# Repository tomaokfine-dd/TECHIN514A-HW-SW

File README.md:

# Screen Usage Load Meter

## 1. Project Overview

### What it does

Screen Usage Load Meter is a two-device system that estimates a user's screen usage load based on ambient light and user presence detection.  
A sensing device placed near a screen detects usage patterns, while a desktop display device visualizes the accumulated load using an analog gauge with a stepper motor and LED indicator.

### General Physical Sketch

The system consists of a small sensing module mounted near a computer screen and a desktop gauge display with a needle and LED.

---

## 2. Sensor Device

The sensor device is a compact, battery-powered module placed near a computer screen.  
It passively detects screen usage behavior without accessing the operating system and wirelessly transmits processed data to the display device via ESP-NOW.

### Sensors and Part Numbers

- **Ambient Light Sensor:** VEML7700 (Adafruit breakout)  
  Used to detect screen-on activity based on lux threshold (< 30 lux = screen off).
- **Time-of-Flight Distance Sensor:** VL53L4CX (Adafruit breakout)  
  Used to detect user presence in front of the screen (> 800mm = no person).

### Processor and Wireless

- **MCU + Wireless:** Seeed Studio XIAO ESP32C3 (ESP32-C3, ESP-NOW over Wi-Fi)

### Power

- 3.7V LiPo battery (1000 mAh)
- Onboard charging via XIAO ESP32C3 built-in battery management

### Sensor Device Sketch

The sensing module is mounted near the display, with the light sensor facing the screen and the distance sensor facing the user.  
The device operates autonomously and does not include user-facing controls.

---

## 3. Display Device

The display device is a desktop physical gauge that visualizes the current screen usage load.  
It integrates a stepper-motor-driven needle and an LED indicator, connected via breadboard prototype.

### Interface Components

- **Stepper Motor:** X27.168 bipolar gauge motor  
  Drives the gauge needle (2° per minute, full range 360°, returns to origin at 180 minutes).
- **LED:** NeoPixel WS2812B (single RGB LED for status indication)  
  Green (0–60 min) → Yellow (60–120 min) → Orange (120–180 min) → Bright Red (180+ min)

### Processor and Wireless

- **MCU + Wireless:** Seeed Studio XIAO ESP32C3  
  Receives data from the sensor device via ESP-NOW and controls motor and LED output.

### Power

- USB 5V (runs alongside computer)

### Display Device Sketch

The display features a gauge with a needle indicating cumulative usage load.  
An LED provides color-coded status, changing color every hour to indicate increasing usage intensity.

---

## 4. Communication and System Diagram

The sensor device continuously transmits processed usage data to the display device using **ESP-NOW** (peer-to-peer Wi-Fi protocol, no router required). The system converts raw sensor signals into a cumulative screen usage time that controls the gauge needle position and LED color state.

**Data Flow:**

1. Sensor signals (ambient light lux + distance mm)
2. Threshold logic (lux < 30 = screen off; distance > 800mm = no person)
3. Usage timer accumulation (seconds counted when both conditions met)
4. ESP-NOW transmission (minutes sent every second to display device)
5. Output mapping to needle position (2°/min) and LED color stage

---

## 5. DSP and Signal Processing Approach

- **DSP:**  
  Dual-threshold detection logic combines ambient light and distance signals. Screen-off state is detected when lux drops below 30. User absence is detected when ToF distance exceeds 800mm. Usage time accumulates only when both sensors confirm active use simultaneously.
- **Note:**  
  No ML model is used in the current implementation. Detection is rule-based with fixed thresholds calibrated to typical indoor desktop environments. False positive rate is approximately 5%, primarily caused by ambient light changes such as overhead lighting.

---

## 6. Datasheets

All component datasheets are included in the `/datasheets` folder, including:

- ESP32-C3 (Seeed Studio XIAO ESP32C3)
- VEML7700 Ambient Light Sensor (Vishay / Adafruit breakout)
- VL53L4CX Time-of-Flight Distance Sensor (ST / Adafruit breakout)
- X27.168 Bipolar Gauge Stepper Motor (Switec/Juken)
- WS2812B RGB LED (NeoPixel)
- Custom Sensor Board PCB (KiCad design files)

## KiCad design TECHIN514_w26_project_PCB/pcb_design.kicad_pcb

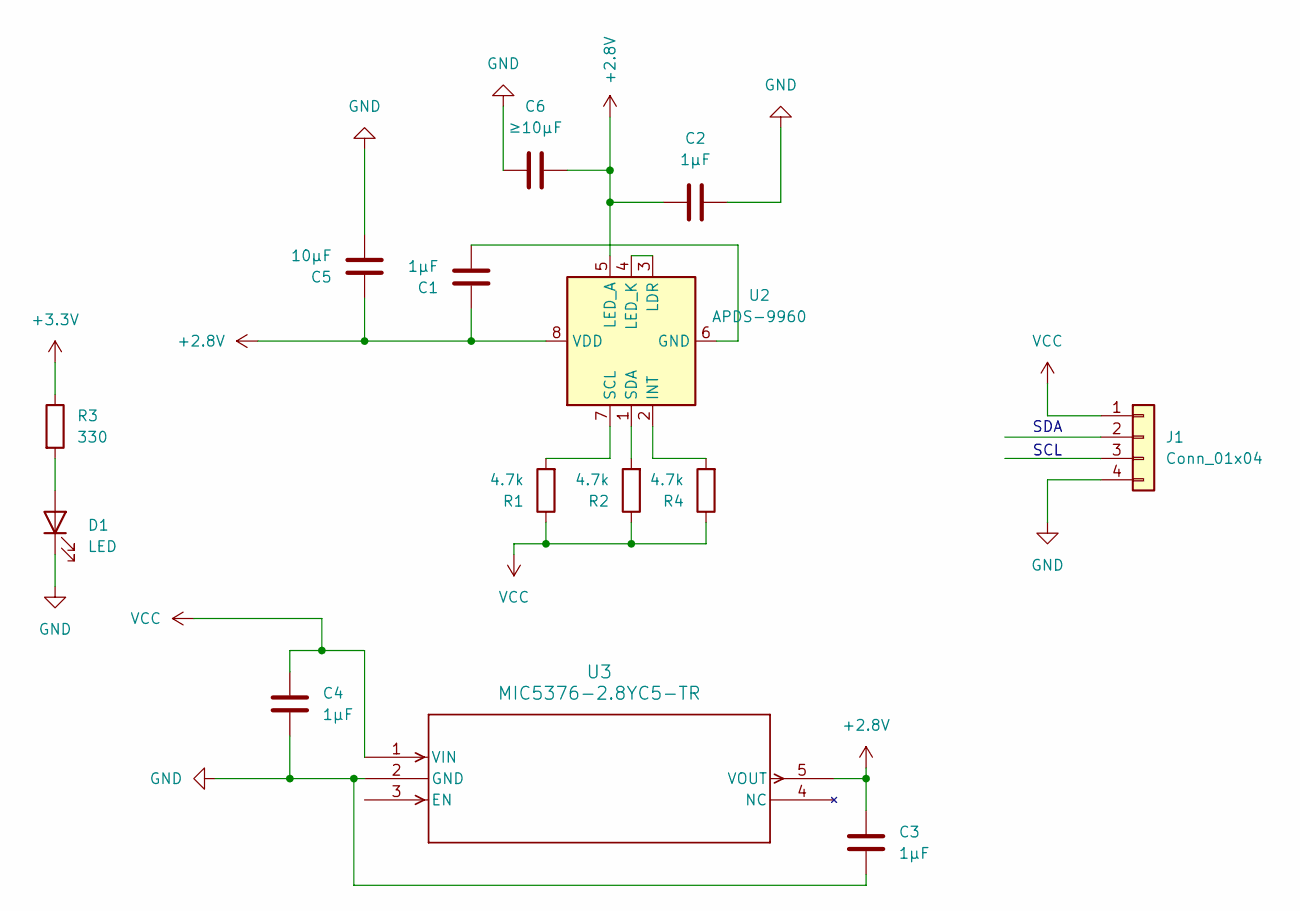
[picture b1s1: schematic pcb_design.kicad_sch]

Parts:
C1, C2, C3, C4: 1μF; C_0603_1608Metric_Pad1.08x0.95mm_HandSolder
C5: 10μF; C_0603_1608Metric_Pad1.08x0.95mm_HandSolder
C6: ≥10µF; C_0603_1608Metric_Pad1.08x0.95mm_HandSolder
D1: LED; LED_0603_1608Metric_Pad1.05x0.95mm_HandSolder
J1: Conn_01x04; PinSocket_1x04_P1.00mm_Vertical
R1, R2, R4: 4.7k; R_0603_1608Metric_Pad0.98x0.95mm_HandSolder
R3: 330; R_0603_1608Metric_Pad0.98x0.95mm_HandSolder
U2: APDS-9960; Avago_APDS-9960
U3: MIC5376-2.8YC5-TR; SC-70_C5_MCH

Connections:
+2.8V: C1.1, C2.1, C3.1, C5.1, C6.1, U2.5 (LED_A), U2.8 (VDD), U3.5 (VOUT)
+3.3V: R3.1
GND: C2.2, C3.2, C4.2, C5.2, C6.2, D1.1 (K), J1.4, U3.2 (GND)
unnamed: D1.2 (A), R3.2
unnamed: C1.2, U2.6 (GND)
unnamed: R4.2, U2.2 (INT)
unnamed: U2.3 (LDR), U2.4 (LED_K)
unnamed: R1.2, U2.7 (SCL)
unnamed: R2.2, U2.1 (SDA)
VCC: C4.1, J1.1, R1.1, R2.1, R4.1, U3.1 (VIN)

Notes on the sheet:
SDA
SCL

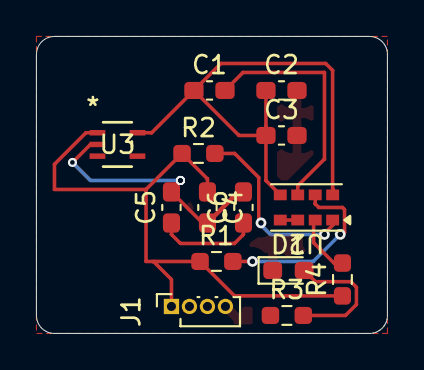
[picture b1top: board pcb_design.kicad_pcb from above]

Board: 2 copper layers, 19.5 x 16.5 mm, 14 parts (0 on the bottom side), 9 nets.

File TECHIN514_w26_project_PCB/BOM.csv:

"Reference","Qty","Value","DNP","Exclude from BOM","Exclude from Board","Footprint","Datasheet"
"C1,C2,C3,C4","4","1μF","","","","Capacitor_SMD:C_0603_1608Metric_Pad1.08x0.95mm_HandSolder","~"
"C5","1","10μF","","","","Capacitor_SMD:C_0603_1608Metric_Pad1.08x0.95mm_HandSolder","~"
"C6","1","≥10µF","","","","Capacitor_SMD:C_0603_1608Metric_Pad1.08x0.95mm_HandSolder","~"
"D1","1","LED","","","","LED_SMD:LED_0603_1608Metric_Pad1.05x0.95mm_HandSolder","~"
"J1","1","Conn_01x04","","","","Connector_PinSocket_1.00mm:PinSocket_1x04_P1.00mm_Vertical","~"
"R1,R2,R4","3","4.7k","","","","Resistor_SMD:R_0603_1608Metric_Pad0.98x0.95mm_HandSolder","~"
"R3","1","330","","","","Resistor_SMD:R_0603_1608Metric_Pad0.98x0.95mm_HandSolder","~"
"U2","1","APDS-9960","","","","Sensor:Avago_APDS-9960","https://docs.broadcom.com/doc/AV02-4191EN"
"U3","1","MIC5376-2.8YC5-TR","","","","APDS-9960:SC-70_C5_MCH","MIC5376-2.8YC5-TR"

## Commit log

2026-01-20 Update GentiamElectronics-28BYJ-48-Stepper-Motor-Datasheet-Rev20220925-final
2026-01-20 upload Aerosemi-MT3608-datasheet
2026-01-26 Create KiCad
2026-01-27 Add placeholder comments to KiCad file
2026-03-16 Revise README for clarity and detail enhancements
    Updated project description, sensor details, and communication method. Enhanced clarity on system components and functionality.
